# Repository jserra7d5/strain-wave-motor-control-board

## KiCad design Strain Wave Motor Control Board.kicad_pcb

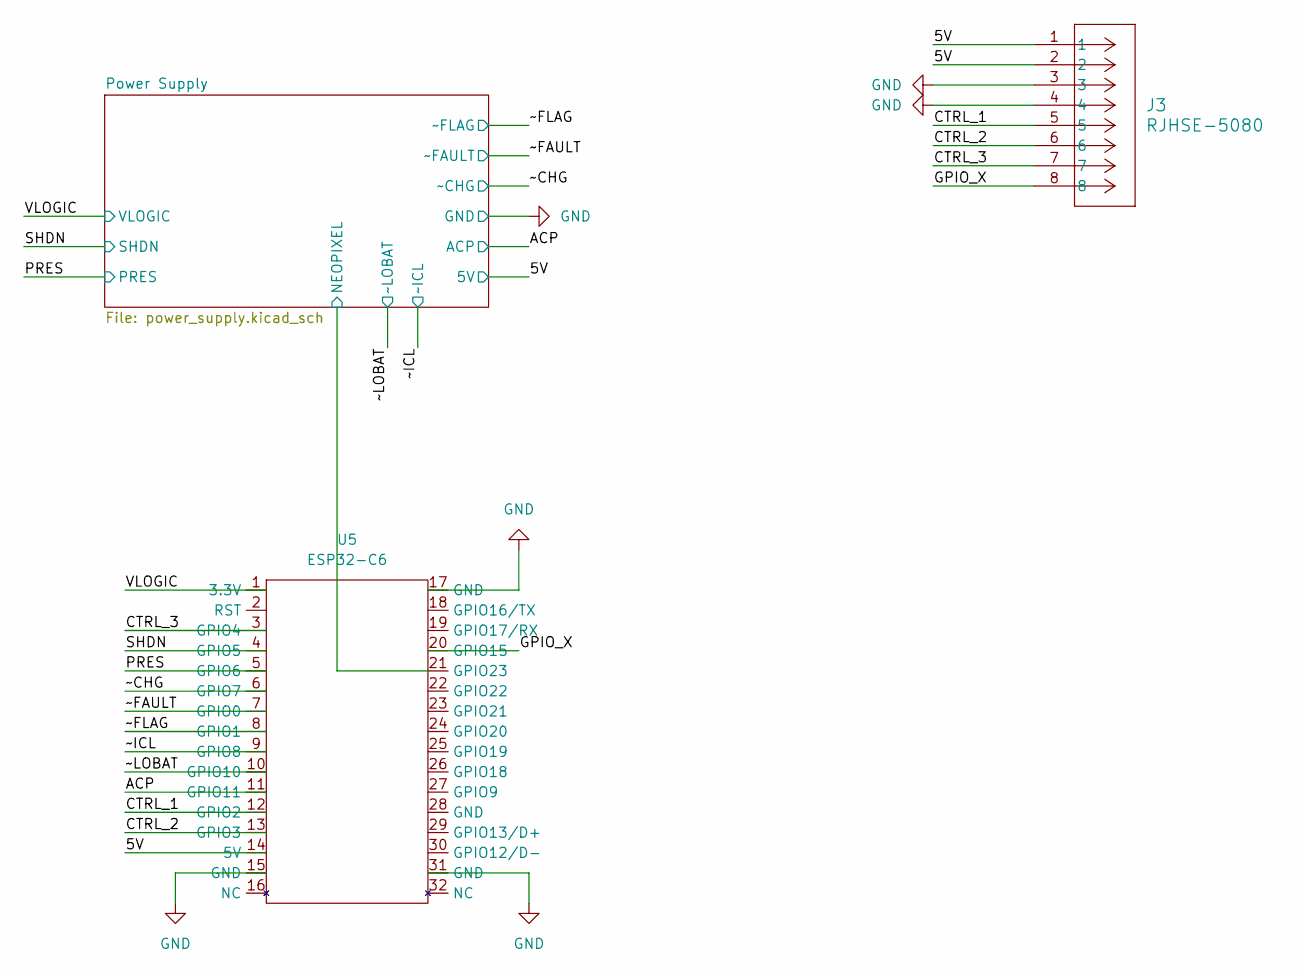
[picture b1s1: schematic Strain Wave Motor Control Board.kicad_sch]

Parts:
J3: RJHSE-5080; CONN_RJSBE5080_16P13X12P57_AMP
U5: ESP32-C6; E

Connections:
/5V: J3.1, J3.2, U5.14 (5V); also elsewhere on the board
/ACP: U5.11 (GPIO11); also elsewhere on the board
/CTRL_1: J3.5, U5.12 (GPIO2)
/CTRL_2: J3.6, U5.13 (GPIO3)
/CTRL_3: J3.7, U5.3 (GPIO4)
/GPIO_X: J3.8, U5.20 (GPIO15)
/PRES: U5.5 (GPIO6)
/Power Supply/NEOPIXEL: U5.21 (GPIO23); also elsewhere on the board
/SHDN: U5.4 (GPIO5); also elsewhere on the board
/VLOGIC: U5.1 (3.3V); also elsewhere on the board
/~CHG: U5.6 (GPIO7); also elsewhere on the board
/~FAULT: U5.7 (GPIO0); also elsewhere on the board
/~FLAG: U5.8 (GPIO1); also elsewhere on the board
/~ICL: U5.9 (GPIO8); also elsewhere on the board
/~LOBAT: U5.10 (GPIO10); also elsewhere on the board
GND: J3.3, J3.4, U5.15 (GND), U5.17 (GND), U5.31 (GND); also elsewhere on the board

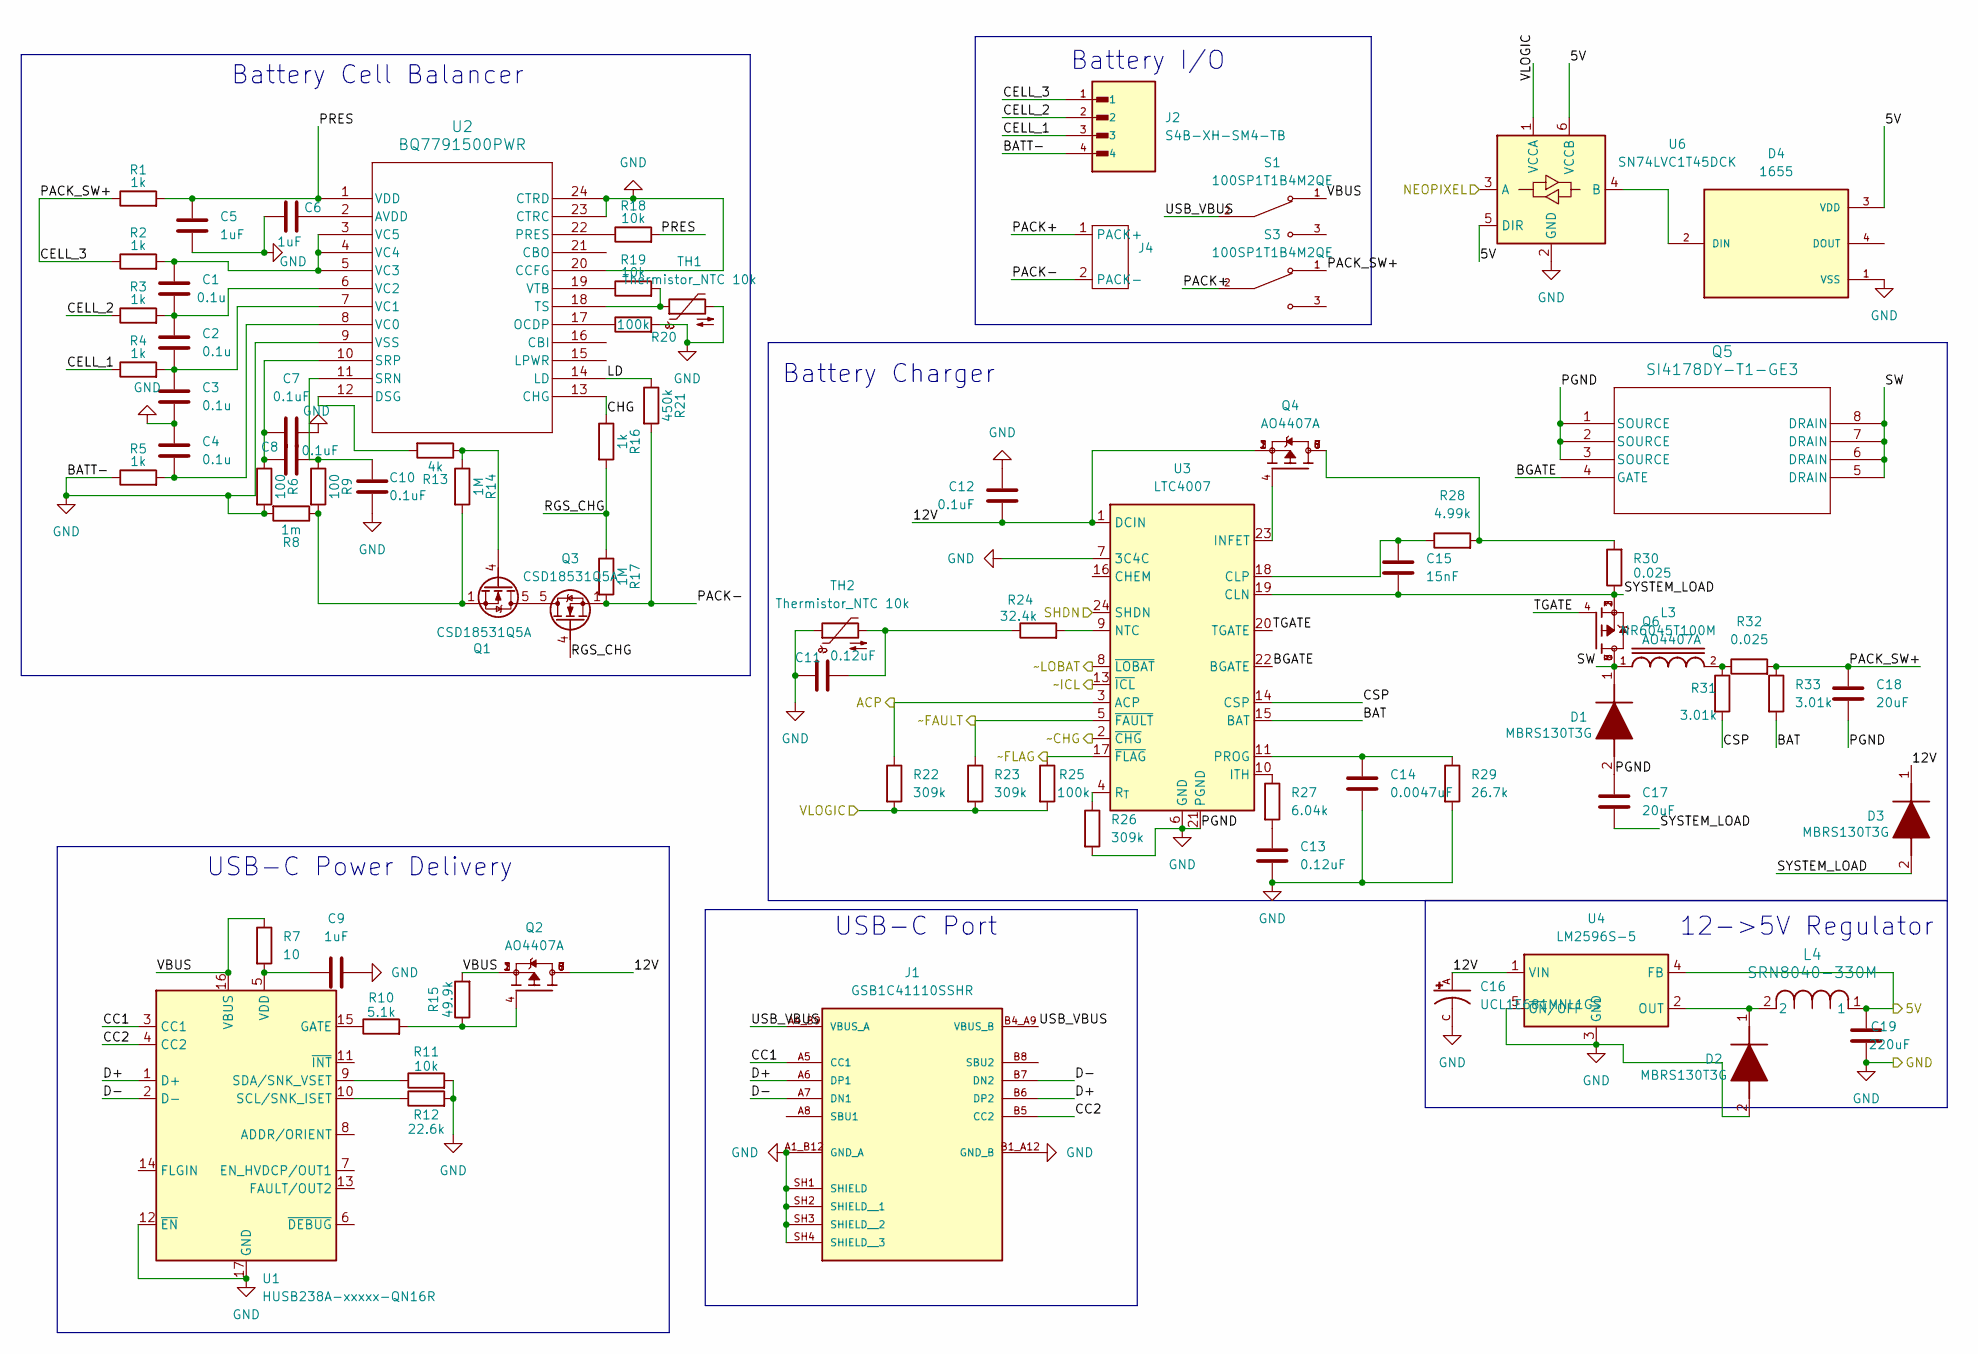
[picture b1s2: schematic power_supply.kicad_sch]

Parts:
C1, C2, C3, C4: 0.1u; LED_0805_2012Metric_Pad1.15x1.40mm_HandSolder
C5, C6, C9: 1uF; C_0603_1608Metric_Pad1.08x0.95mm_HandSolder
C7, C8, C10, C12: 0.1uF; LED_0805_2012Metric_Pad1.15x1.40mm_HandSolder
C11, C13: 0.12uF; LED_0805_2012Metric_Pad1.15x1.40mm_HandSolder
C14: 0.0047uF; C_0603_1608Metric_Pad1.08x0.95mm_HandSolder
C15: 15nF; C_0603_1608Metric_Pad1.08x0.95mm_HandSolder
C16: UCL1E681MNL1GS; CAPAE1030X1350N
C17, C18: 20uF; C_0805_2012Metric_Pad1.18x1.45mm_HandSolder
C19: 220uF; C_1206_3216Metric_Pad1.33x1.80mm_HandSolder
D1, D2, D3: MBRS130T3G; DIOM5436X247N; Manufacturer_Part_Number MBRS130T3G; Mouser Part Number 863-MBRS130T3G
D4: 1655; LED_1655; PARTREV 01
J1: GSB1C41110SSHR; AMPHENOL_GSB1C41110SSHR; PARTREV AX1
J2: S4B-XH-SM4-TB; JST_S4B-XH-SM4-TB; PARTREV NA
J4: LiPo Wire Pads
L3: NR6045T100M; IND_NR6045T100M; PARTREV NA
L4: SRN8040-330M; IND_BOURNS_SRN8040
Q1, Q3: CSD18531Q5A; TDSON-8-1
Q2, Q4, Q6: AO4407A; SOIC127P600X175-8N; PARTREV I
Q5: SI4178DY-T1-GE3; SOIC_Y-T1-GE3_VIS
R1, R2, R3, R4, R5, R16: 1k; R_0805_2012Metric_Pad1.20x1.40mm_HandSolder
R6, R9: 100; R_0805_2012Metric_Pad1.20x1.40mm_HandSolder
R7: 10; R_0805_2012Metric_Pad1.20x1.40mm_HandSolder
R8: 1m; R_0805_2012Metric_Pad1.20x1.40mm_HandSolder
R10: 5.1k; R_0805_2012Metric_Pad1.20x1.40mm_HandSolder
R11, R18, R19: 10k; R_0805_2012Metric_Pad1.20x1.40mm_HandSolder
R12: 22.6k; R_0805_2012Metric_Pad1.20x1.40mm_HandSolder
R13: 4k; R_0805_2012Metric_Pad1.20x1.40mm_HandSolder
R14, R17: 1M; R_0805_2012Metric_Pad1.20x1.40mm_HandSolder
R15: 49.9k; R_0805_2012Metric_Pad1.20x1.40mm_HandSolder
R20, R25: 100k; R_0805_2012Metric_Pad1.20x1.40mm_HandSolder
R21: 450k; R_0805_2012Metric_Pad1.20x1.40mm_HandSolder
R22, R23, R26: 309k; R_0805_2012Metric_Pad1.20x1.40mm_HandSolder
R24: 32.4k; R_0805_2012Metric_Pad1.20x1.40mm_HandSolder
R27: 6.04k; R_0805_2012Metric_Pad1.20x1.40mm_HandSolder
R28: 4.99k; R_0805_2012Metric_Pad1.20x1.40mm_HandSolder
R29: 26.7k; R_0805_2012Metric_Pad1.20x1.40mm_HandSolder
R30, R32: 0.025; R_0805_2012Metric_Pad1.20x1.40mm_HandSolder
R31, R33: 3.01k; R_0805_2012Metric_Pad1.20x1.40mm_HandSolder
S1, S3: 100SP1T1B4M2QE; SW_100SP1T1B4M2QE; PARTREV E
TH1, TH2: Thermistor_NTC 10k; R_0402_1005Metric_Pad0.72x0.64mm_HandSolder
U1: HUSB238A-xxxxx-QN16R; WQFN-16-1EP_3x3mm_P0.5mm_EP1.75x1.75mm
U2: BQ7791500PWR; PW24_TEX
U3: LTC4007; SSOP-24_3.9x8.7mm_P0.635mm
U4: LM2596S-5; TO-263-5_TabPin3
U6: SN74LVC1T45DCK; SOT-363_SC-70-6

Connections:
/5V: C19.1, D4.3 (VDD), L4.1, U4.4 (FB), U6.5 (DIR), U6.6 (VCCB); also elsewhere on the board
/ACP: R22.1, U3.3 (ACP); also elsewhere on the board
/Power Supply/12V: C12.2, C16.A, D3.1 (K), Q2.5, Q2.6, Q2.7, Q2.8, Q4.1, Q4.2, Q4.3, U3.1 (DCIN), U4.1 (VIN)
/Power Supply/BAT: R33.2, U3.15 (BAT)
/Power Supply/BGATE: Q5.4 (GATE), U3.22 (BGATE)
/Power Supply/CC1: J1.A5 (CC1), U1.3 (CC1)
/Power Supply/CC2: J1.B5 (CC2), U1.4 (CC2)
/Power Supply/CELL_1: J2.3, R4.1
/Power Supply/CELL_2: J2.2, R3.1
/Power Supply/CELL_3: C18.1, J2.1, R1.1, R2.1, R32.2, R33.1, S3.1
/Power Supply/CHG: R16.1, U2.13 (CHG)
/Power Supply/CSP: R31.2, U3.14 (CSP)
/Power Supply/D+: J1.A6 (DP1), J1.B6 (DP2), U1.1 (D+)
/Power Supply/D-: J1.A7 (DN1), J1.B7 (DN2), U1.2 (D-)
/Power Supply/LD: R21.1, U2.14 (LD)
/Power Supply/NEOPIXEL: U6.3 (A); also elsewhere on the board
/Power Supply/PACK+: J4.1 (PACK+), S3.2
/Power Supply/PACK-: J4.2 (PACK-), Q3.1 (S), Q3.2 (S), Q3.3 (S), R17.2, R21.2
/Power Supply/PRES: C5.1, R1.2, R18.2, U2.1 (VDD)
/Power Supply/RGS_CHG: Q3.4 (G), R16.2, R17.1
/Power Supply/SW: D1.1 (K), L3.1, Q5.5 (DRAIN), Q5.6 (DRAIN), Q5.7 (DRAIN), Q5.8 (DRAIN), Q6.5, Q6.6, Q6.7, Q6.8
/Power Supply/SYSTEM_LOAD: C15.2, C17.2, D3.2 (A), Q6.1, Q6.2, Q6.3, R30.1, U3.19 (CLN)
/Power Supply/TGATE: Q6.4, U3.20 (TGATE)
/Power Supply/USB_VBUS: J1.A4_B9 (VBUS_A), J1.B4_A9 (VBUS_B), S1.2
/Power Supply/VBUS: Q2.1, Q2.2, Q2.3, R7.1, R15.2, S1.1, U1.16 (VBUS)
/SHDN: U3.24 (SHDN); also elsewhere on the board
/VLOGIC: R22.2, R23.2, R25.2, U6.1 (VCCA); also elsewhere on the board
/~CHG: U3.2 (~CHG); also elsewhere on the board
/~FAULT: R23.1, U3.5 (~FAULT); also elsewhere on the board
/~FLAG: R25.1, U3.17 (~FLAG); also elsewhere on the board
/~ICL: U3.13 (~ICL); also elsewhere on the board
/~LOBAT: U3.8 (~LOBAT); also elsewhere on the board
GND: C3.2, C4.1, C5.2, C6.1, C7.2, C9.2, C10.2, C11.1, C12.1, C13.2, C14.2, C16.C, C17.1, C18.2, C19.2, D1.2 (A), D2.2 (A), D4.1 (VSS), J1.A1_B12 (GND_A), J1.B1_A12 (GND_B), J1.SH1 (SHIELD), J1.SH2 (SHIELD__1), J1.SH3 (SHIELD__2), J1.SH4 (SHIELD__3), J2.4, Q5.1 (SOURCE), Q5.2 (SOURCE), Q5.3 (SOURCE), R5.1, R6.2, R8.2, R11.2, R12.2, R20.2, R26.2, R29.2, TH1.2, TH2.1, U1.12 (~EN), U1.17 (GND), U2.9 (VSS), U2.20 (CCFG), U2.23 (CTRC), U2.24 (CTRD), U3.6 (GND), U3.7 (3C4C), U3.21 (PGND), U4.3 (GND), U4.5 (~ON/OFF), U6.2 (GND); also elsewhere on the board
unnamed: C11.2, R24.1, TH2.2
unnamed: C13.1, R27.2
unnamed: D2.1 (K), L4.2, U4.2 (OUT)
unnamed: D4.2 (DIN), U6.4 (B)
unnamed: L3.2, R31.1, R32.1
unnamed: Q1.5 (D), Q3.5 (D)
unnamed: Q1.4 (G), R13.1, R14.1
unnamed: Q1.1 (S), Q1.2 (S), Q1.3 (S), R8.1, R9.2, R14.2
unnamed: Q2.4, R10.2, R15.1
unnamed: Q4.5, Q4.6, Q4.7, Q4.8, R28.2, R30.2
unnamed: R10.1, U1.15 (GATE)
unnamed: R12.1, U1.10 (SCL/SNK_ISET)
unnamed: R11.1, U1.9 (SDA/SNK_VSET)
unnamed: C9.1, R7.2, U1.5 (VDD)
unnamed: C6.2, U2.2 (AVDD)
unnamed: R13.2, U2.12 (DSG)
unnamed: R20.1, U2.17 (OCDP)
unnamed: R18.1, U2.22 (PRES)
unnamed: C8.2, C10.1, R9.1, U2.11 (SRN)
unnamed: C7.1, C8.1, R6.1, U2.10 (SRP)
unnamed: R19.2, TH1.1, U2.18 (TS)
unnamed: C4.2, R5.2, U2.8 (VC0)
unnamed: C2.2, C3.1, R4.2, U2.7 (VC1)
unnamed: C1.2, C2.1, R3.2, U2.6 (VC2)
unnamed: C1.1, R2.2, U2.3 (VC5), U2.4 (VC4), U2.5 (VC3)
unnamed: R19.1, U2.19 (VTB)
unnamed: C15.1, R28.1, U3.18 (CLP)
unnamed: Q4.4, U3.23 (INFET)
unnamed: R27.1, U3.10 (ITH)
unnamed: R24.2, U3.9 (NTC)
unnamed: C14.1, R29.1, U3.11 (PROG)
unnamed: R26.1, U3.4 (R_{T})

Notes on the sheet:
Battery Charger
Battery I/O
USB-C Power Delivery
USB-C Port
12->5V Regulator
Battery Cell Balancer

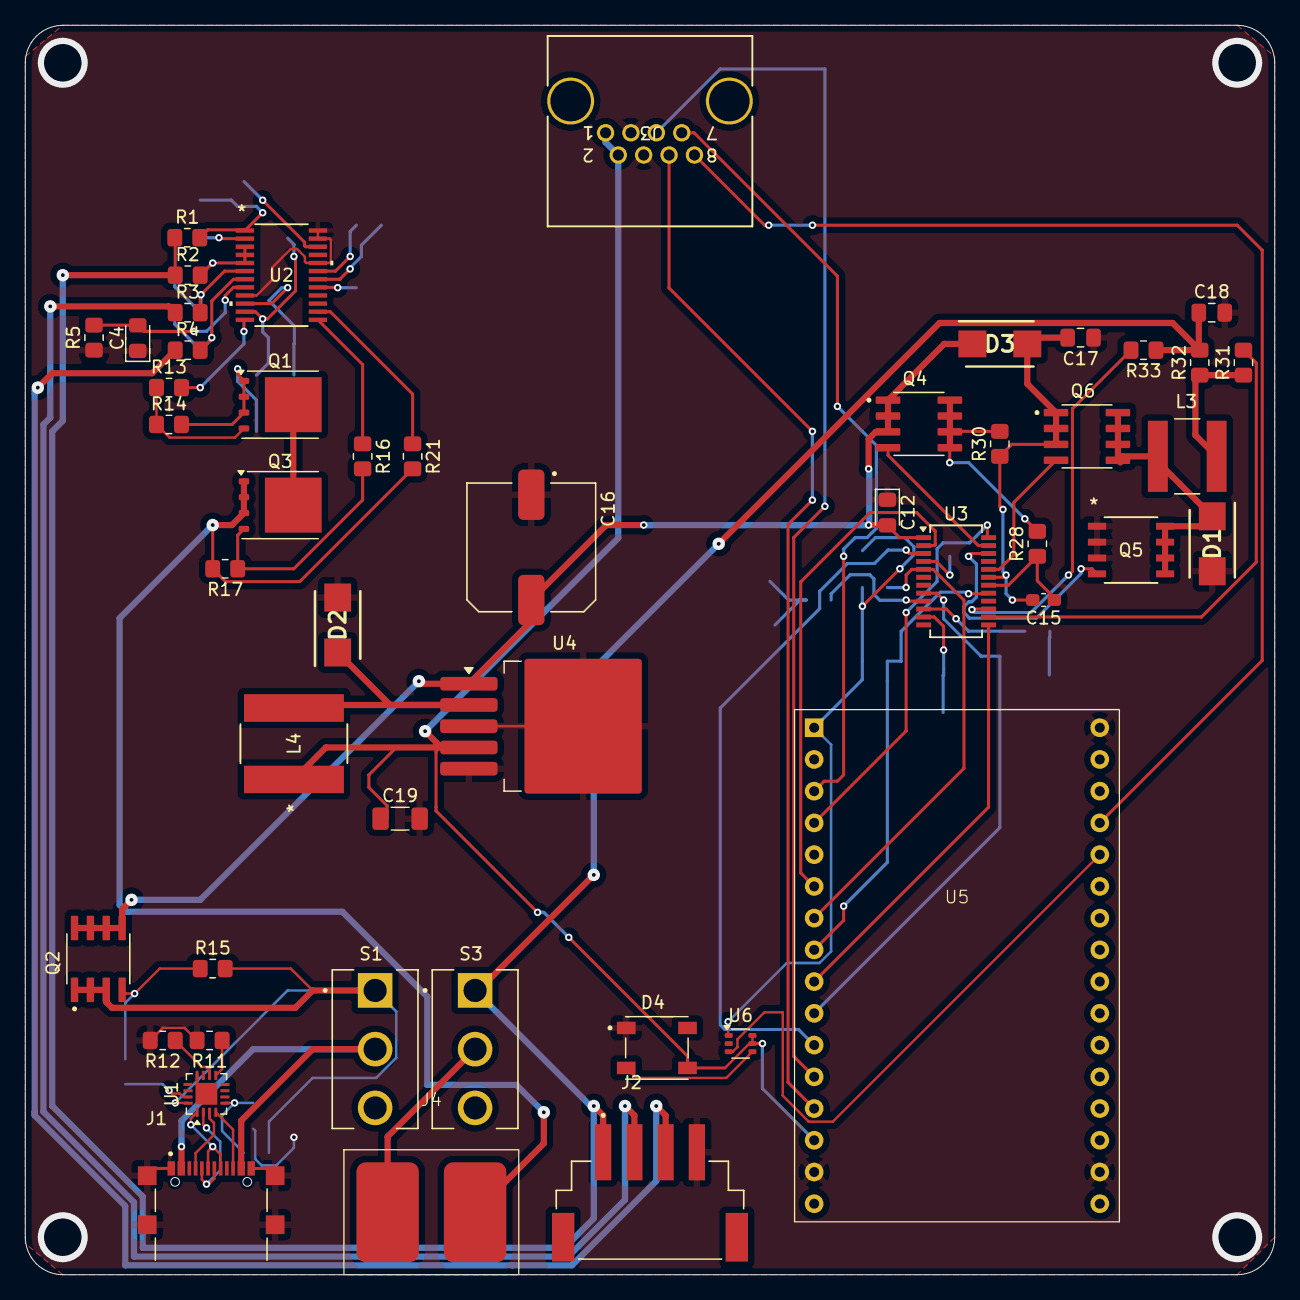
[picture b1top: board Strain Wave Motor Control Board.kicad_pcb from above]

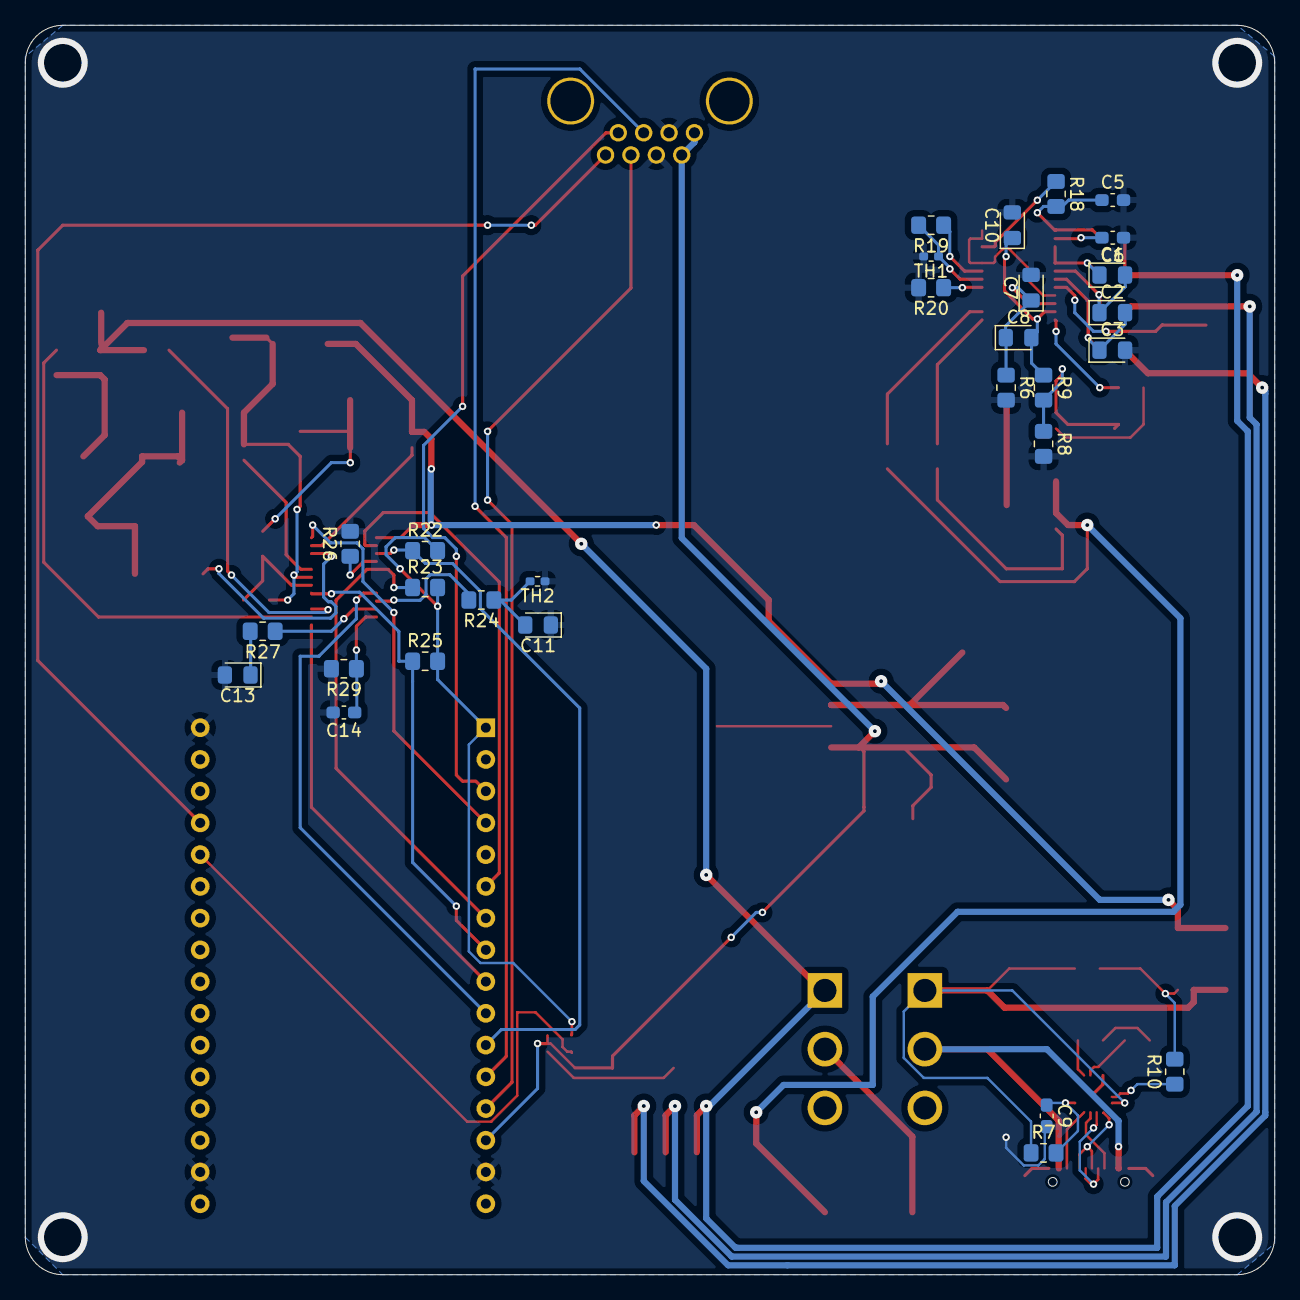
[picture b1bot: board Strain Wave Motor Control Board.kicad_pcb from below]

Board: 2 copper layers, 100.0 x 100.0 mm, 78 parts (29 on the bottom side), 69 nets.

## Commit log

2025-10-10 added sub-schematics
2025-10-17 add library from macbook
2025-10-17 LTC4007 done, BQ7791 halfway implemented
2025-10-17 final commit before bed
2025-10-21 power supply schematic done
2025-10-24 commit check
2025-10-24 add H-bridge schematic
2025-10-24 add shcematic labels
2025-10-27 footprint issues solved
2025-10-27 ESP32 schematic added
2025-10-31 started layout
2025-11-03 done
